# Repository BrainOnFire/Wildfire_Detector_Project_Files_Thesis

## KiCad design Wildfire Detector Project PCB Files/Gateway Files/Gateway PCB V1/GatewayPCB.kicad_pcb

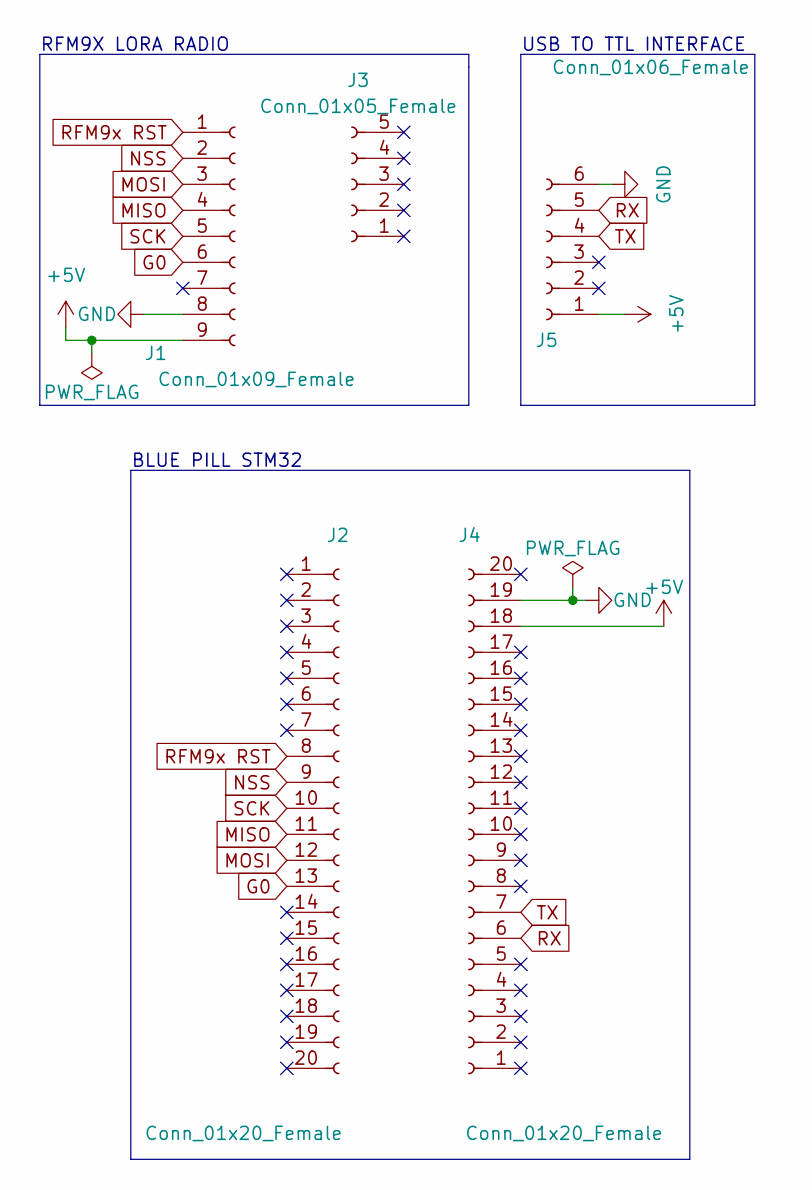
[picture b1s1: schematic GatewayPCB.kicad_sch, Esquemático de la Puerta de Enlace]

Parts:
J1: Conn_01x09_Female; PinSocket_1x09_P2.54mm_Vertical
J2, J4: Conn_01x20_Female; PinSocket_1x20_P2.54mm_Vertical
J3: Conn_01x05_Female; PinSocket_1x05_P2.54mm_Vertical
J5: Conn_01x06_Female; PinSocket_1x06_P2.54mm_Horizontal

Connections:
+5V: J1.9, J4.18, J5.1
G0: J1.6, J2.13
GND: J1.8, J4.19, J5.6
MISO: J1.4, J2.11
MOSI: J1.3, J2.12
NSS: J1.2, J2.9
RFM9x RST: J1.1, J2.8
RX: J4.6, J5.5
SCK: J1.5, J2.10
TX: J4.7, J5.4

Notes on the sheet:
RFM9X LORA RADIO
USB TO TTL INTERFACE
BLUE PILL STM32

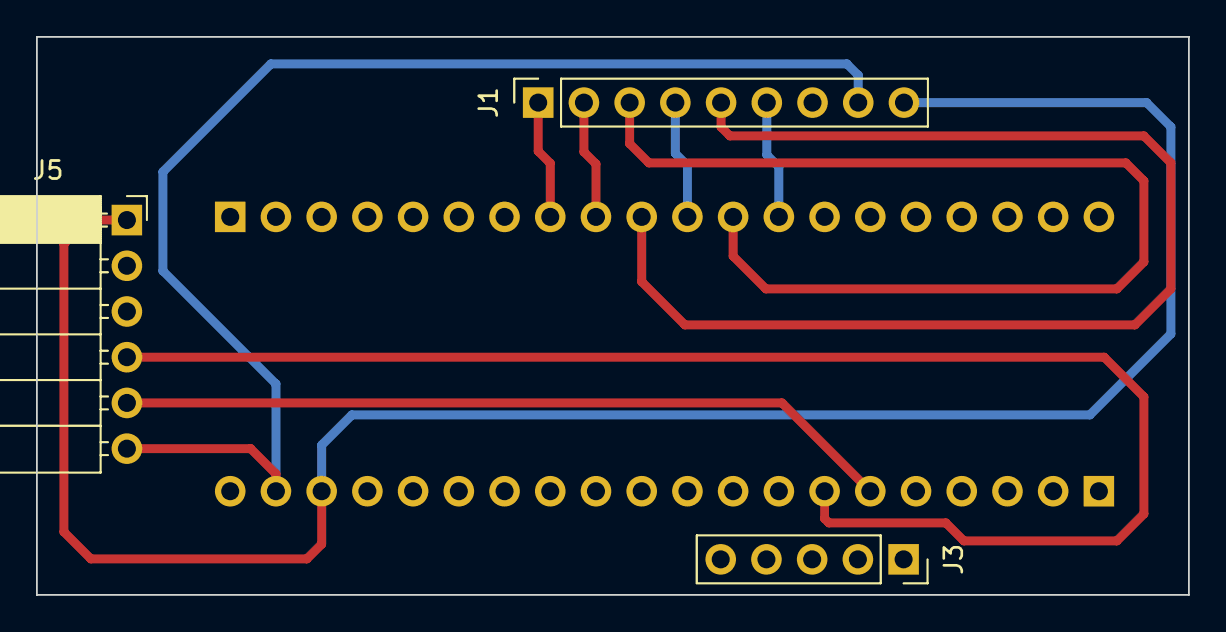
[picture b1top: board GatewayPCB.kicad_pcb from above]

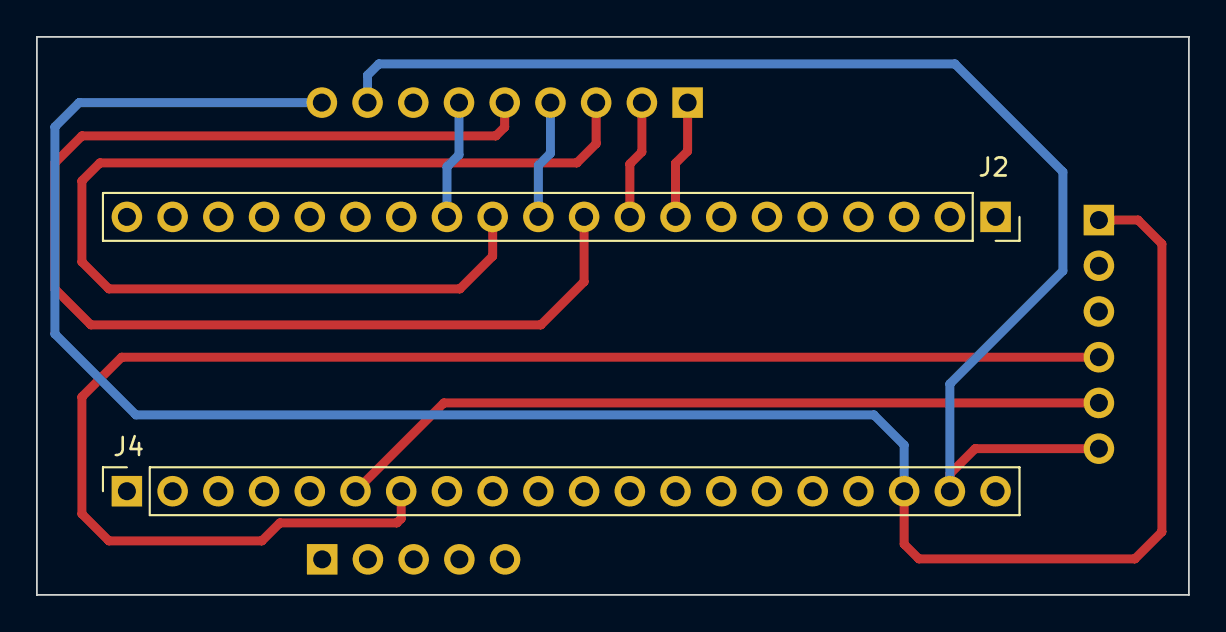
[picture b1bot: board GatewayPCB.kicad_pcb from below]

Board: 2 copper layers, 64.0 x 31.0 mm, 5 parts (2 on the bottom side), 10 nets.

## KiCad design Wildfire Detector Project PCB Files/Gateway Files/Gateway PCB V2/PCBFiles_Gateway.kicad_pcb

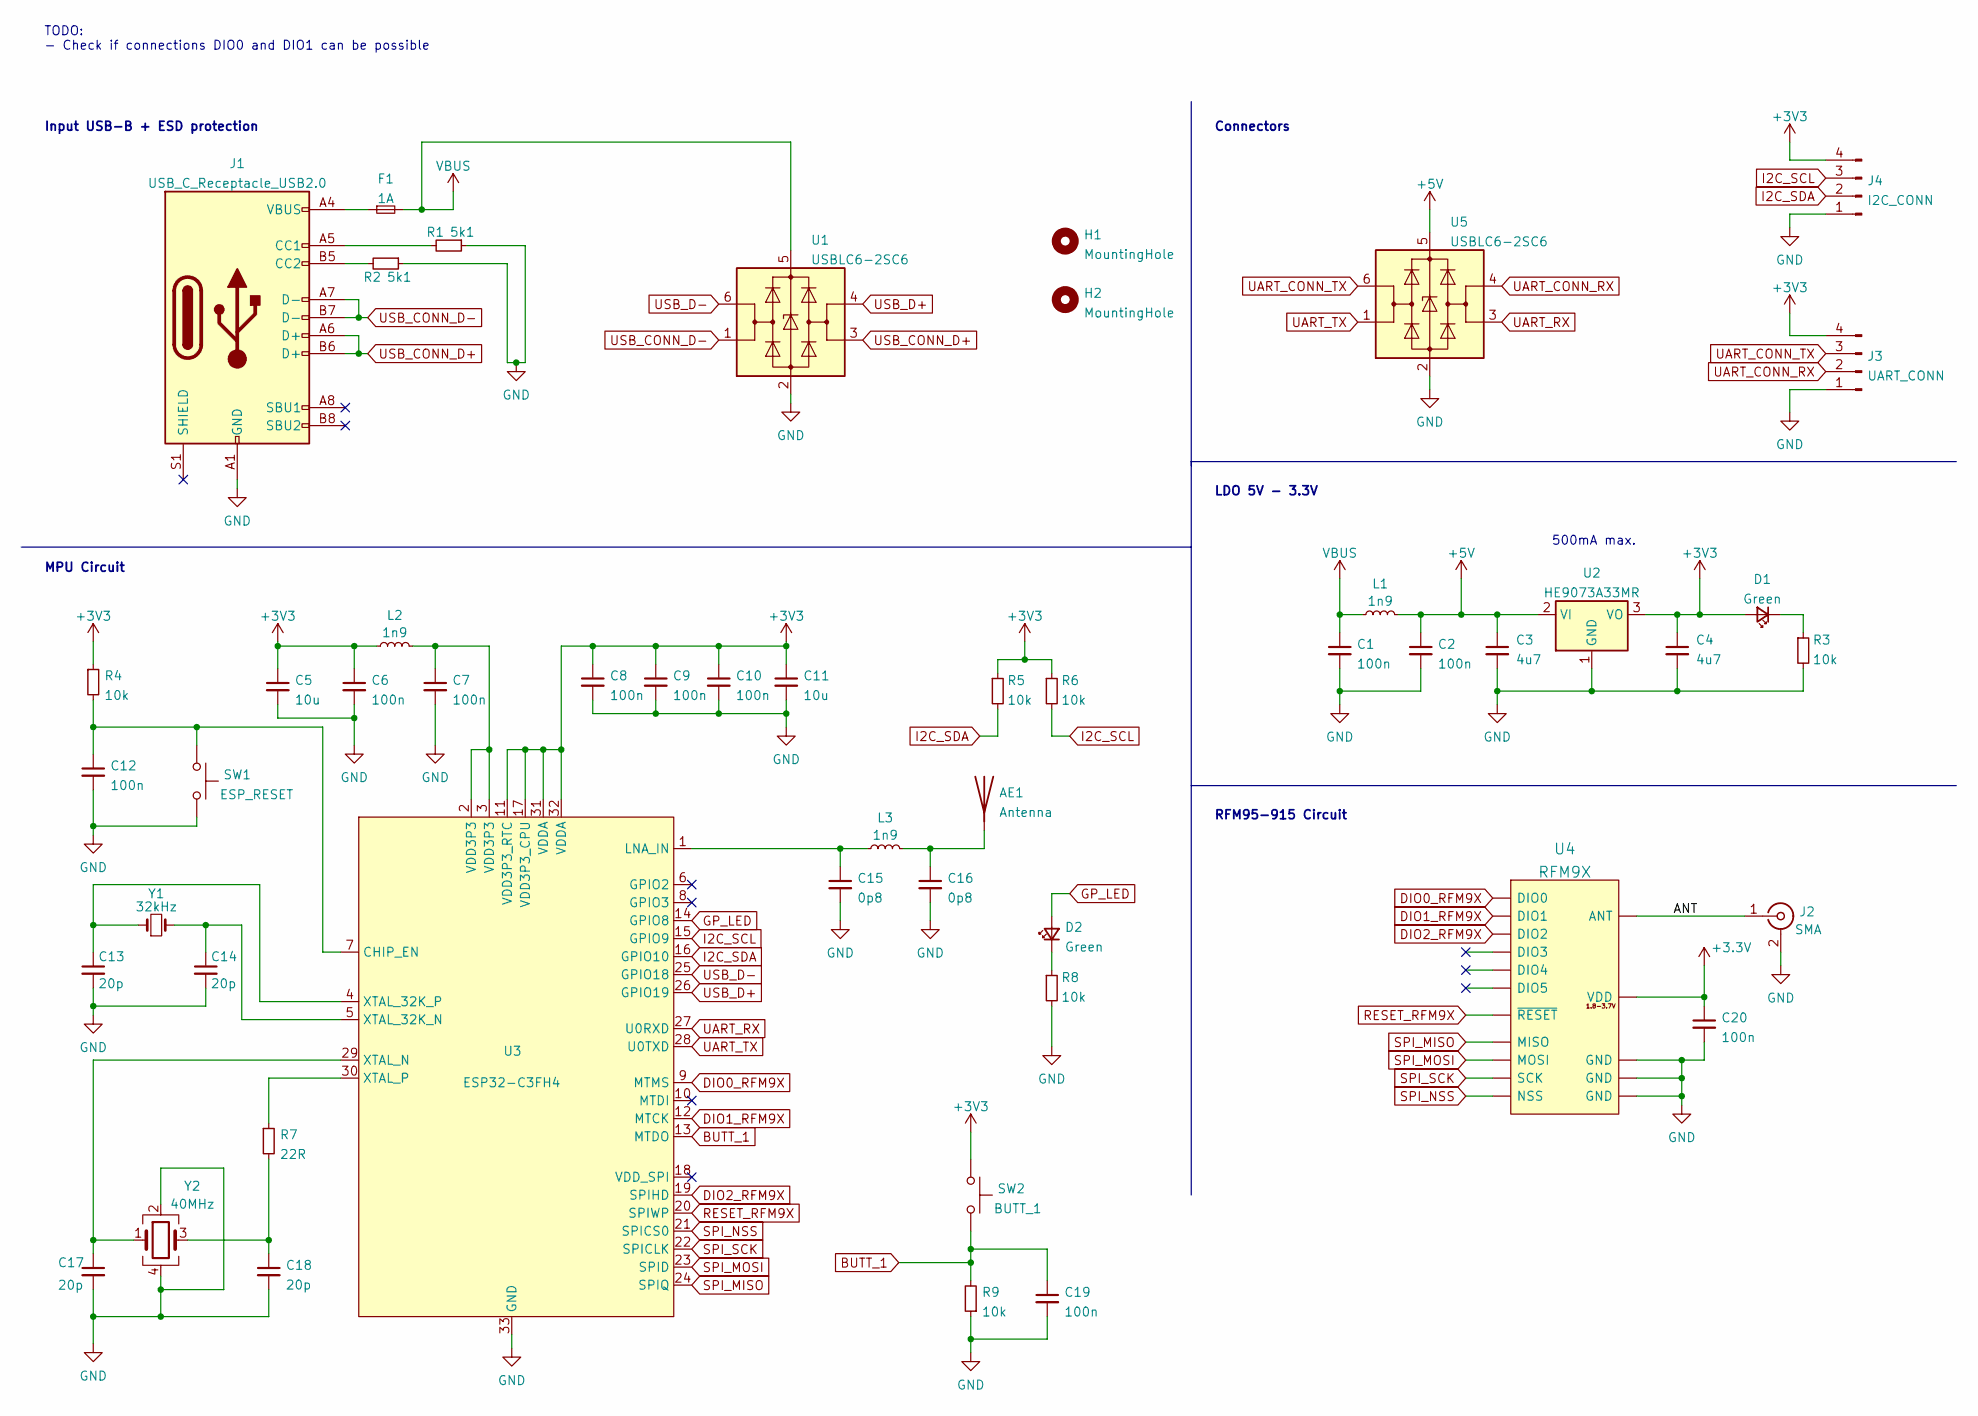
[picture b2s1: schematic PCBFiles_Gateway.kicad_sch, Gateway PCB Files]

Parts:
AE1: Antenna; PCB Meander Antenna
C1, C2: 100n; C_1206_3216Metric
C3, C4: 4u7; C_1206_3216Metric
C5, C11: 10u; C_0402_1005Metric
C6, C7, C8, C9, C10, C12, C19, C20: 100n; C_0402_1005Metric
C13, C14, C17, C18: 20p; C_0402_1005Metric
C15, C16: 0p8; C_0402_1005Metric
D1, D2: Green; C_0603_1608Metric
F1: 1A; Fuse_0603_1608Metric
H1, H2: MountingHole; MountingHole_2.2mm_M2_Pad
J1: USB_C_Receptacle_USB2.0; USB_C_Receptacle_HRO_TYPE-C-31-M-12
J2: SMA; SMA_Samtec_SMA-J-P-X-ST-EM1_EdgeMount
J3: UART_CONN; Molex_KK-254_AE-6410-04A_1x04_P2.54mm_Vertical
J4: I2C_CONN; PinHeader_1x04_P2.54mm_Vertical
L1, L2, L3: 1n9; L_0402_1005Metric
R1, R2: 5k1; R_0402_1005Metric
R3, R4, R5, R6, R8, R9: 10k; R_0805_2012Metric
R7: 22R; R_0402_1005Metric
SW1: ESP_RESET; SW_SPST_B3U-1000P
SW2: BUTT_1; SW_SPST_B3U-1000P
U1, U5: USBLC6-2SC6; SOT-23-6
U2: HE9073A33MR; SOT-23
U3: ESP32-C3FH4; QFN-32-1EP_5x5mm_P0.5mm_EP3.7x3.7mm
U4: RFM9X; RFM9X-SMD; LCSC Part # C2844473
Y1: 32kHz; Crystal_SMD_3215-2Pin_3.2x1.5mm
Y2: 40MHz; Crystal_SMD_3225-4Pin_3.2x2.5mm

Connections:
+5V: C2.1, C3.1, L1.2, U2.2 (VI), U5.5 (VBUS)
/ANT: J2.1 (In), U4.9 (ANT)
BUTT_1: C19.1, R9.2, SW2.2, U3.13 (MTDO)
DIO0_RFM9X: U3.9 (MTMS), U4.14 (DIO0)
DIO1_RFM9X: U3.12 (MTCK), U4.15 (DIO1)
DIO2_RFM9X: U3.19 (SPIHD), U4.16 (DIO2)
GND: C1.2, C2.2, C3.2, C4.2, C5.2, C6.2, C7.2, C8.2, C9.2, C10.2, C11.2, C12.2, C13.2, C14.2, C15.2, C16.2, C17.2, C18.2, C19.2, C20.2, J1.A1 (GND), J1.A12 (GND), J1.B1 (GND), J1.B12 (GND), J2.2 (Ext), J3.1, J4.1, R1.1, R2.1, R3.2, R8.2, R9.1, SW1.2, U1.2 (GND), U2.1 (GND), U3.33 (GND), U4.1 (GND), U4.8 (GND), U4.10 (GND), U5.2 (GND), Y2.2, Y2.4
GP_LED: D2.2 (A), U3.14 (GPIO8)
I2C_SCL: J4.3, R6.2, U3.15 (GPIO9)
I2C_SDA: J4.2, R5.2, U3.16 (GPIO10)
unnamed: C7.1, L2.2, U3.2 (VDD3P3), U3.3 (VDD3P3)
unnamed: C12.1, R4.2, SW1.1, U3.7 (CHIP_EN)
unnamed: C13.1, U3.4 (XTAL_32K_P), Y1.1
unnamed: C14.1, U3.5 (XTAL_32K_N), Y1.2
unnamed: C15.1, L3.1, U3.1 (LNA_IN)
unnamed: AE1.1 (A), C16.1, L3.2
unnamed: C17.1, U3.29 (XTAL_N), Y2.1
unnamed: C18.1, R7.2, Y2.3
unnamed: D1.1 (K), R3.1
unnamed: D2.1 (K), R8.1
unnamed: F1.1, J1.A4 (VBUS), J1.A9 (VBUS), J1.B4 (VBUS), J1.B9 (VBUS)
unnamed: J1.A5 (CC1), R1.2
unnamed: J1.B5 (CC2), R2.2
unnamed: R7.1, U3.30 (XTAL_P)
RESET_RFM9X: U3.20 (SPIWP), U4.6 (~RESET)
SPI_MISO: U3.24 (SPIQ), U4.2 (MISO)
SPI_MOSI: U3.23 (SPID), U4.3 (MOSI)
SPI_NSS: U3.21 (SPICS0), U4.5 (NSS)
SPI_SCK: U3.22 (SPICLK), U4.4 (SCK)
UART_CONN_RX: J3.2, U5.4 (I/O2)
UART_CONN_TX: J3.3, U5.6 (I/O1)
UART_RX: U3.27 (U0RXD), U5.3 (I/O2)
UART_TX: U3.28 (U0TXD), U5.1 (I/O1)
USB_CONN_D+: J1.A6 (D+), J1.B6 (D+), U1.3 (I/O2)
USB_CONN_D-: J1.A7 (D-), J1.B7 (D-), U1.1 (I/O1)
USB_D+: U1.4 (I/O2), U3.26 (GPIO19)
USB_D-: U1.6 (I/O1), U3.25 (GPIO18)
VBUS: C1.1, F1.2, L1.1, U1.5 (VBUS)

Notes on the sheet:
Connectors
RFM95-915 Circuit
500mA max.
MPU Circuit
TODO: - Check if connections DIO0 and DIO1 can be possible
LDO 5V - 3.3V
Input USB-B + ESD protection

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
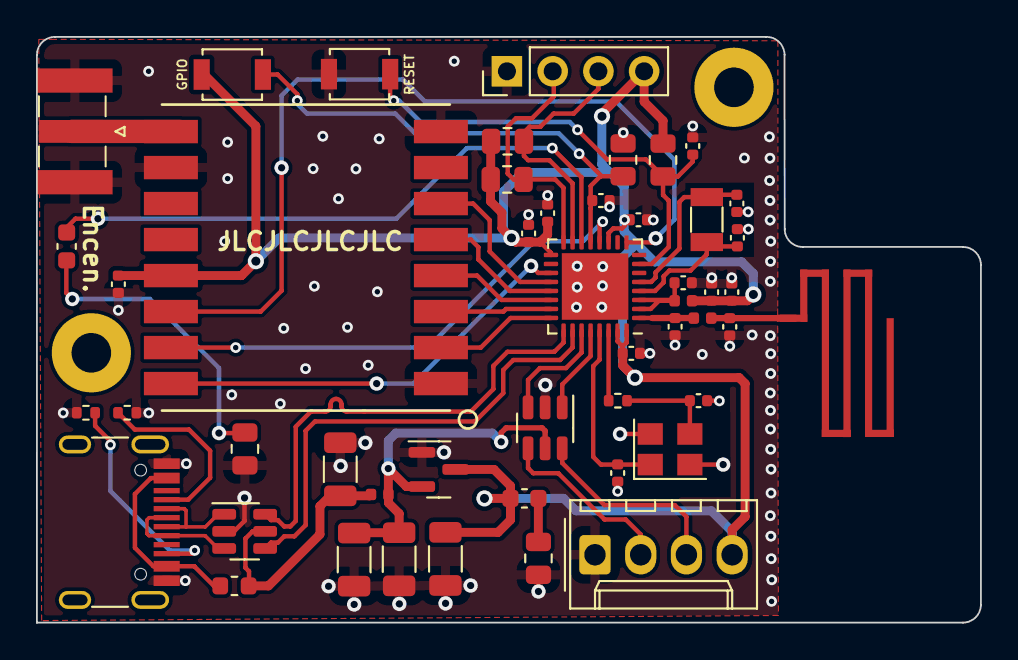
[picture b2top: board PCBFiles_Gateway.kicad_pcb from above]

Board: 4 copper layers, 52.4 x 32.5 mm, 51 parts (0 on the bottom side), 39 nets.

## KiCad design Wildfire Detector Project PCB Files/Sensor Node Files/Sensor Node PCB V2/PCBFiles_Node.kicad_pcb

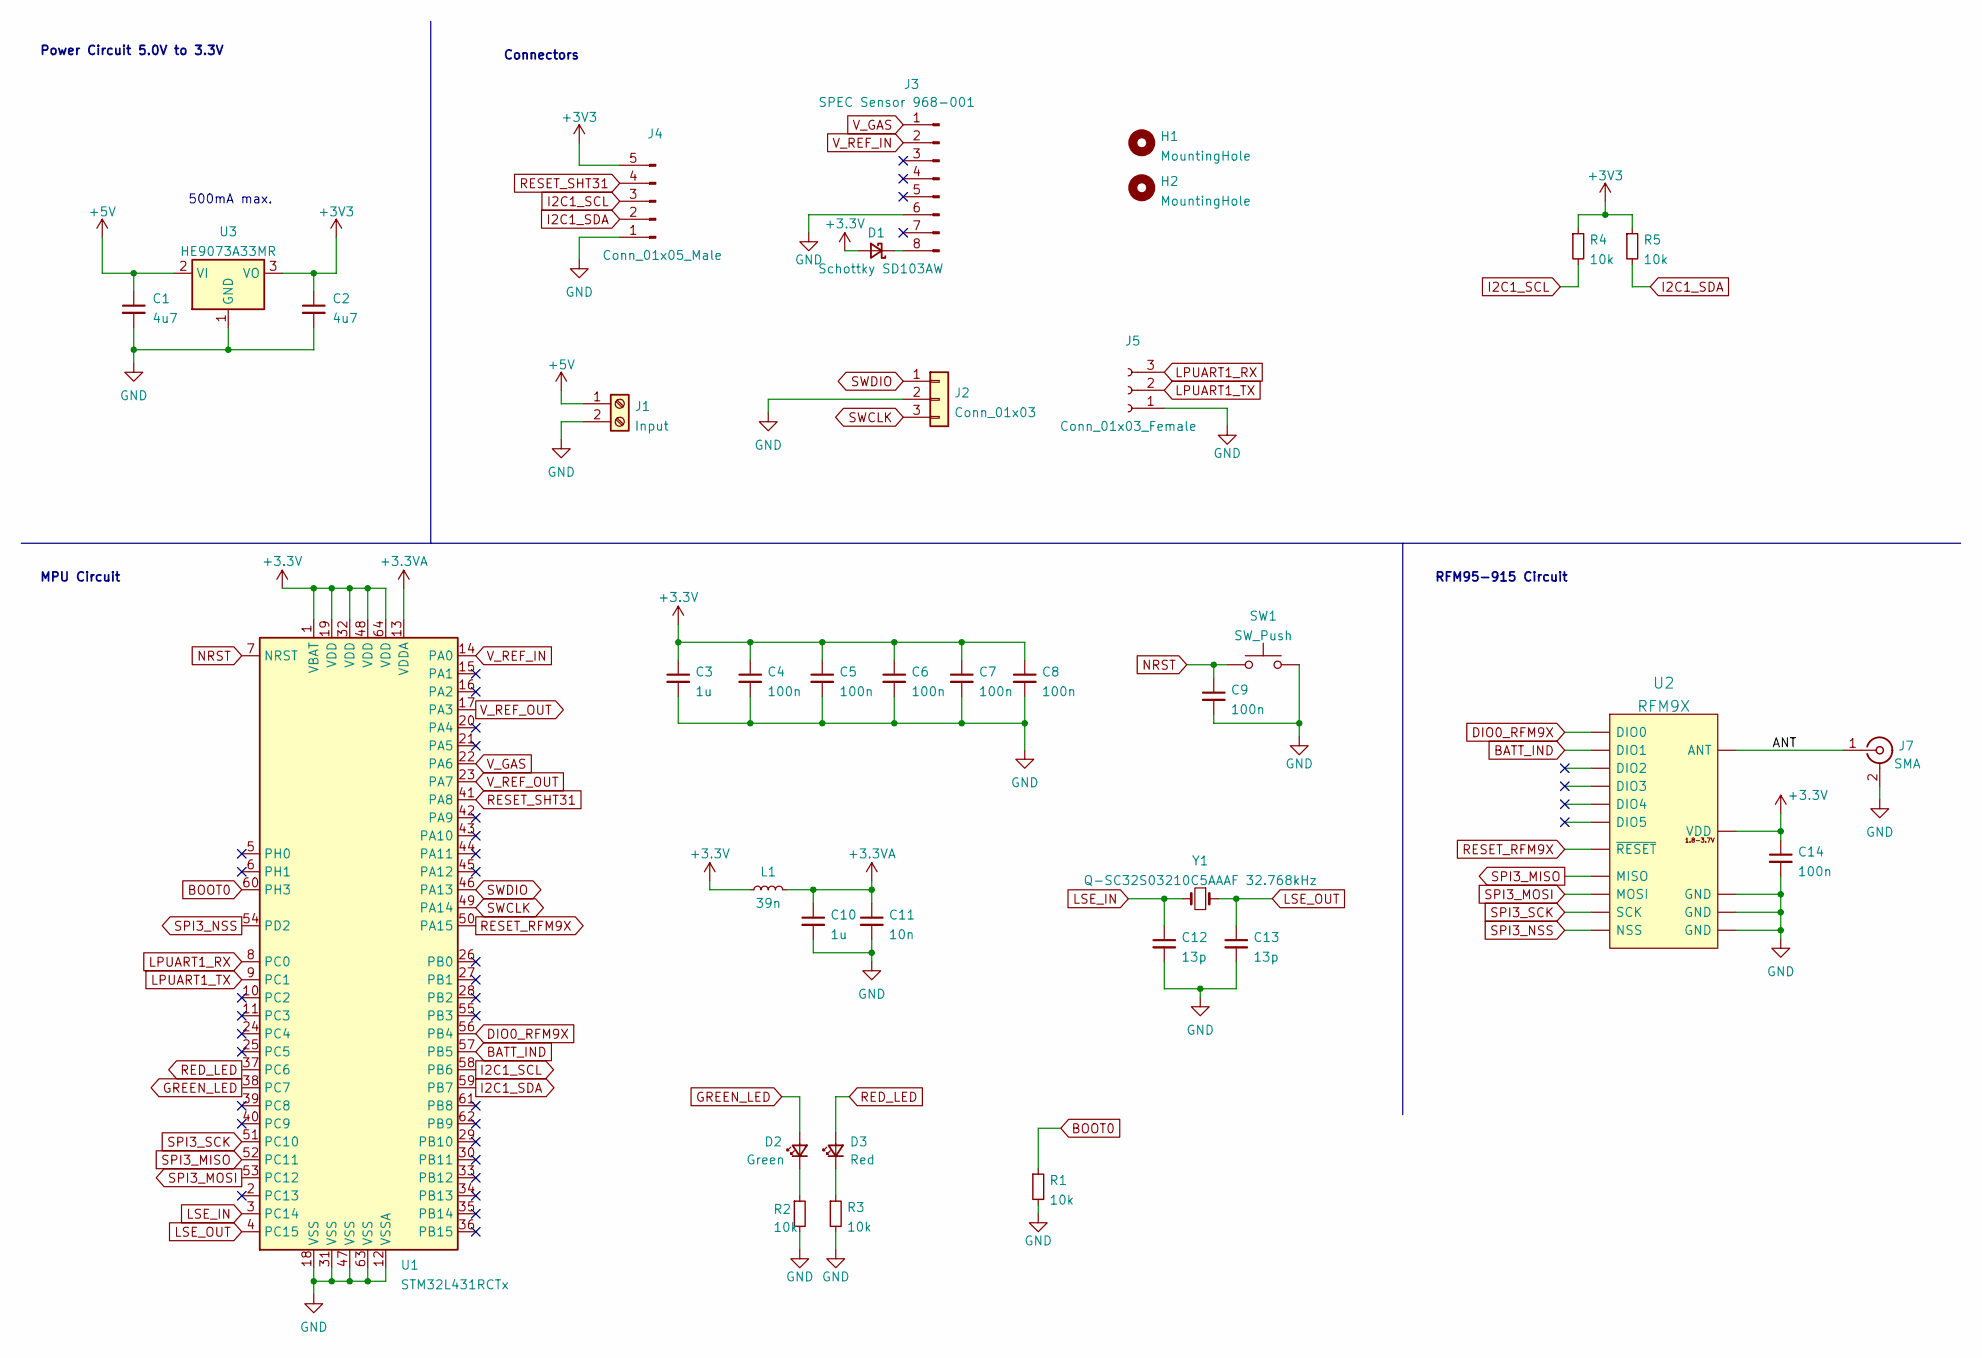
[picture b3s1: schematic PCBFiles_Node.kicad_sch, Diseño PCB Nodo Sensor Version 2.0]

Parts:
C1, C2: 4u7; C_1206_3216Metric
C3, C10: 1u; C_0402_1005Metric; LCSC Part # C52923
C4, C5, C6, C7, C8, C9, C14: 100n; C_0402_1005Metric; LCSC Part # C307331
C11: 10n; C_0402_1005Metric; LCSC Part # C15195
C12, C13: 13p; C_0402_1005Metric; LCSC Part # C48936
D1: Schottky SD103AW; D_SOD-123; LCSC Part # C191023
D2: Green; LED_0603_1608Metric; LCSC Part # C118334
D3: Red; LED_0603_1608Metric; LCSC Part # C118330
H1, H2: MountingHole; MountingHole_2.2mm_M2_Pad
J1: Input; TerminalBlock_bornier-2_P5.08mm
J2: Conn_01x03; PinSocket_1x03_P2.54mm_Vertical
J3: SPEC Sensor 968-001; PinHeader_1x08_P2.54mm_Horizontal
J4: Conn_01x05_Male; PinSocket_1x05_P2.54mm_Vertical
J5: Conn_01x03_Female; PinSocket_1x03_P2.54mm_Horizontal
J7: SMA; SMA_Samtec_SMA-J-P-X-ST-EM1_EdgeMount
L1: 39n; L_0402_1005Metric; LCSC Part # C335623
R1: 10k; R_0805_2012Metric; LCSC Part # C25744
R2, R3, R4, R5: 10k; R_0805_2012Metric; LCSC Part # C21190
SW1: SW_Push; SW_SPST_B3U-1000P; LCSC Part # B3U-1000P
U1: STM32L431RCTx; LQFP-64_10x10mm_P0.5mm; LCSC Part # C92468
U2: RFM9X; RFM9X-SMD; LCSC Part # C2844473
U3: HE9073A33MR; SOT-23
Y1: Q-SC32S03210C5AAAF 32.768kHz; Q13FC1350000400; LCSC Part # C32346

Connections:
+3.3VA: C10.1, C11.1, L1.2, U1.13 (VDDA)
+5V: C1.1, J1.1, U3.2 (VI)
/ANT: J7.1 (In), U2.16 (ANT)
BATT_IND: U1.57 (PB5), U2.10 (DIO1)
BOOT0: R1.1, U1.60 (PH3)
DIO0_RFM9X: U1.56 (PB4), U2.11 (DIO0)
GND: C1.2, C2.2, C3.2, C4.2, C5.2, C6.2, C7.2, C8.2, C9.2, C10.2, C11.2, C12.2, C13.2, C14.2, J1.2, J2.2, J3.6, J4.1, J5.1, J7.2 (Ext), R1.2, R2.2, R3.2, SW1.2, U1.12 (VSSA), U1.18 (VSS), U1.31 (VSS), U1.47 (VSS), U1.63 (VSS), U2.1 (GND), U2.8 (GND), U2.15 (GND), U3.1 (GND)
GREEN_LED: D2.2 (A), U1.38 (PC7)
I2C1_SCL: J4.3, R4.2, U1.58 (PB6)
I2C1_SDA: J4.2, R5.2, U1.59 (PB7)
LPUART1_RX: J5.3, U1.8 (PC0)
LPUART1_TX: J5.2, U1.9 (PC1)
LSE_IN: C12.1, U1.3 (PC14), Y1.2
LSE_OUT: C13.1, U1.4 (PC15), Y1.1
NRST: C9.1, SW1.1, U1.7 (NRST)
unnamed: D1.1 (K), J3.8
unnamed: D2.1 (K), R2.1
unnamed: D3.1 (K), R3.1
RED_LED: D3.2 (A), U1.37 (PC6)
RESET_RFM9X: U1.50 (PA15), U2.6 (~RESET)
RESET_SHT31: J4.4, U1.41 (PA8)
SPI3_MISO: U1.52 (PC11), U2.2 (MISO)
SPI3_MOSI: U1.53 (PC12), U2.3 (MOSI)
SPI3_NSS: U1.54 (PD2), U2.5 (NSS)
SPI3_SCK: U1.51 (PC10), U2.4 (SCK)
SWCLK: J2.3, U1.49 (PA14)
SWDIO: J2.1, U1.46 (PA13)
V_GAS: J3.1, U1.22 (PA6)
V_REF_IN: J3.2, U1.14 (PA0)
V_REF_OUT: U1.17 (PA3), U1.23 (PA7)

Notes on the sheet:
RFM95-915 Circuit
500mA max.
MPU Circuit
Connectors
Power Circuit 5.0V to 3.3V

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
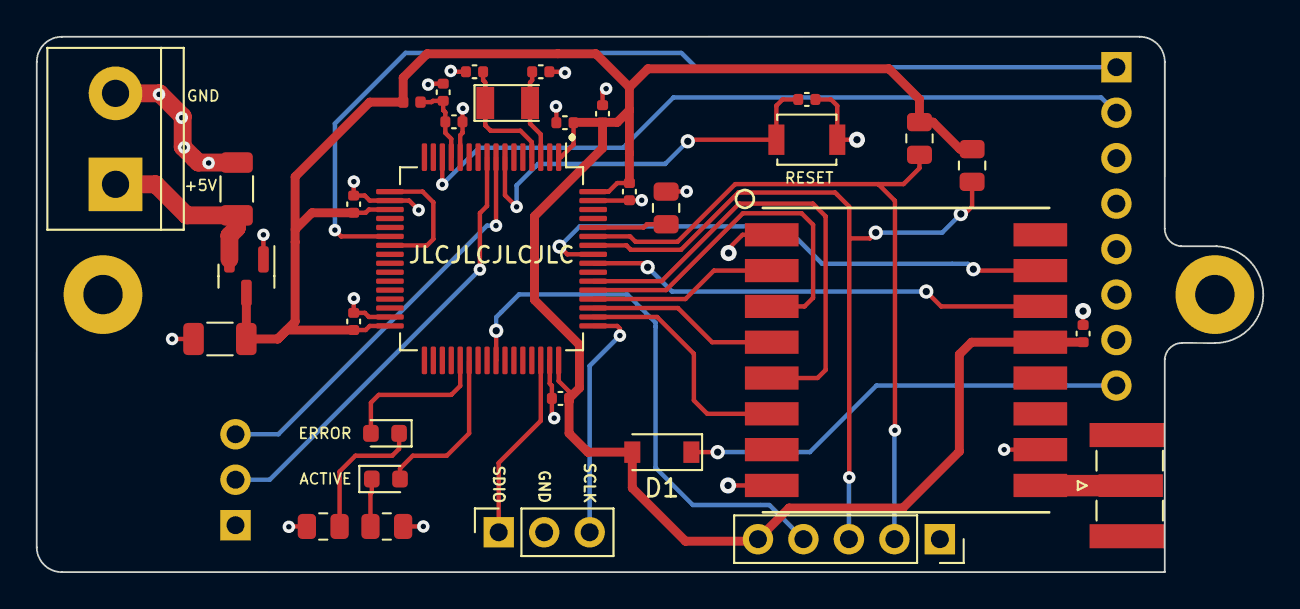
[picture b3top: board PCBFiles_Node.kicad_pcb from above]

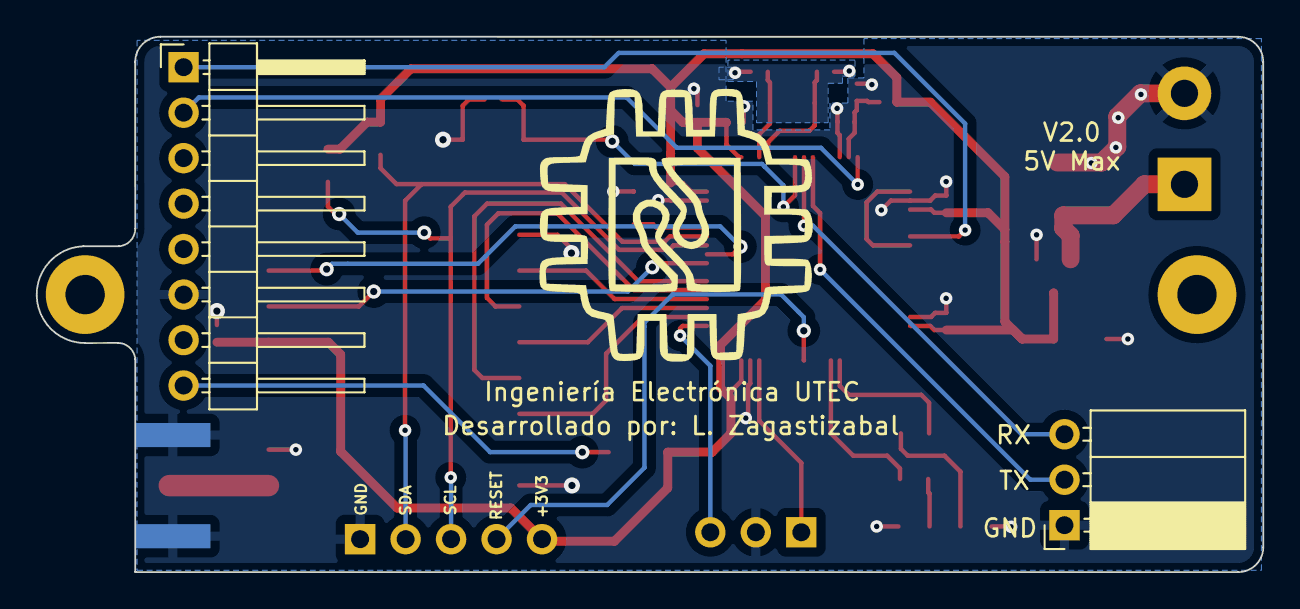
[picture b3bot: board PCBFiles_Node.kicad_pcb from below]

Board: 2 copper layers, 68.5 x 29.9 mm, 36 parts (2 on the bottom side), 31 nets.

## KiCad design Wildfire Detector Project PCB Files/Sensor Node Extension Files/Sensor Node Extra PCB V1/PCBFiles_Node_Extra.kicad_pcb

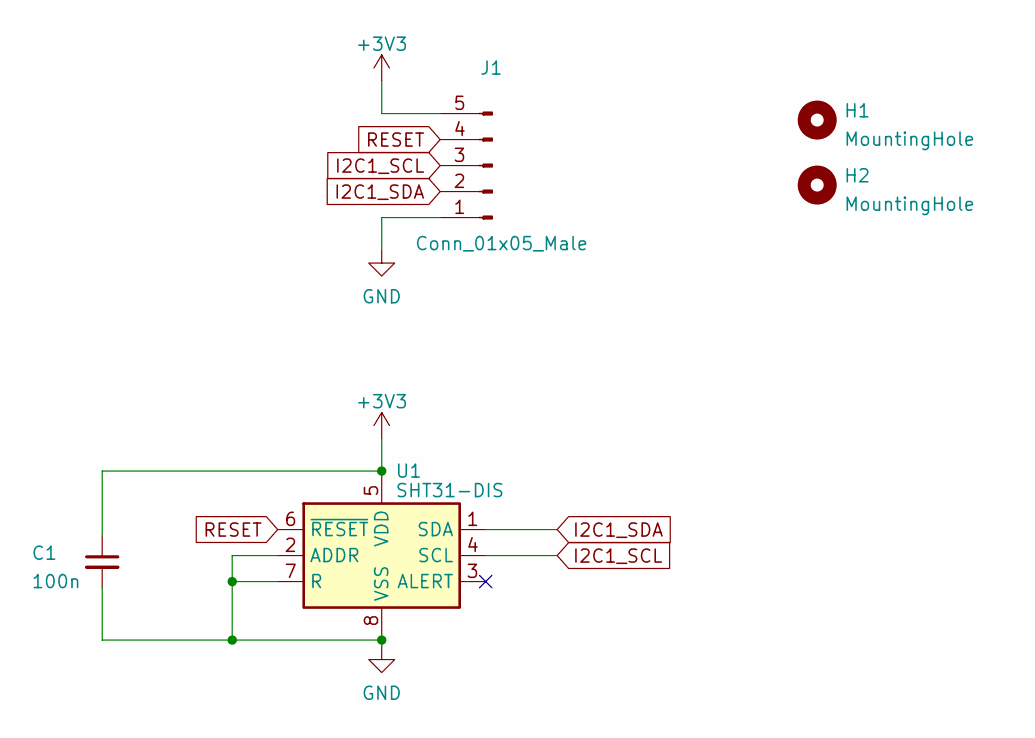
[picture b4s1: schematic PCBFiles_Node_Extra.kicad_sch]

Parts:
C1: 100n; C_0402_1005Metric; LCSC Part # C307331
H1, H2: MountingHole; MountingHole_2.2mm_M2_Pad
J1: Conn_01x05_Male; PinSocket_1x05_P2.54mm_Vertical
U1: SHT31-DIS; Sensirion_DFN-8-1EP_2.5x2.5mm_P0.5mm_EP1.1x1.7mm

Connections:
+3V3: C1.1, J1.5, U1.5 (VDD)
GND: C1.2, J1.1, U1.2 (ADDR), U1.7 (R), U1.8 (VSS), U1.9 (VSS)
I2C1_SCL: J1.3, U1.4 (SCL)
I2C1_SDA: J1.2, U1.1 (SDA)
RESET: J1.4, U1.6 (~RESET)

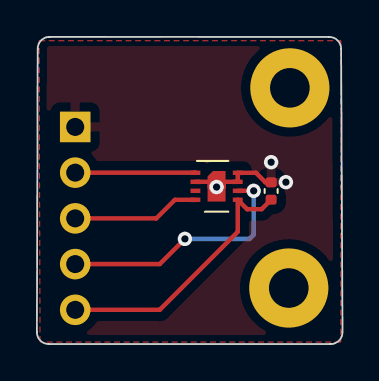
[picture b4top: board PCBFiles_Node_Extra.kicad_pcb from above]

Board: 2 copper layers, 17.0 x 17.1 mm, 5 parts (1 on the bottom side), 5 nets.

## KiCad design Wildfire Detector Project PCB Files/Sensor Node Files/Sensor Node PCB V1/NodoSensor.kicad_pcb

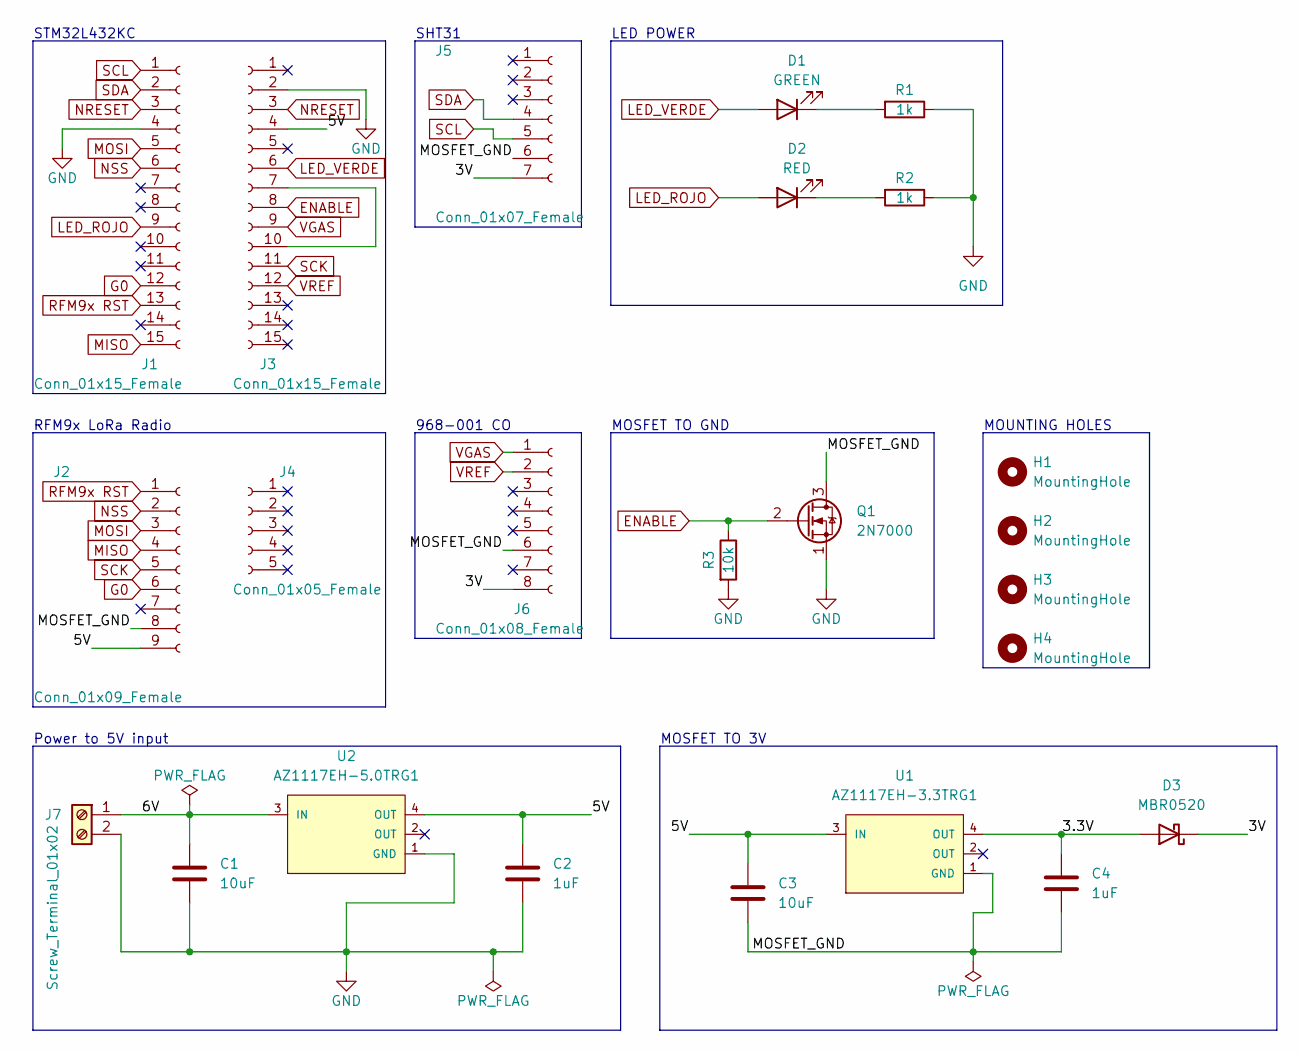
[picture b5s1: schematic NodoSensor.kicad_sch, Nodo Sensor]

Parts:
C1, C3: 10uF; CP_Radial_D5.0mm_P2.50mm
C2, C4: 1uF; CP_Radial_D5.0mm_P2.50mm
D1: GREEN; LED_D5.0mm
D2: RED; LED_D5.0mm
D3: MBR0520; D_SOD-123
H1, H2, H3, H4: MountingHole; MountingHole_3.2mm_M3
J1, J3: Conn_01x15_Female; PinSocket_1x15_P2.54mm_Vertical
J2: Conn_01x09_Female; PinSocket_1x09_P2.54mm_Vertical
J4: Conn_01x05_Female; PinSocket_1x05_P2.54mm_Vertical
J5: Conn_01x07_Female; PinSocket_1x07_P2.54mm_Vertical
J6: Conn_01x08_Female; PinSocket_1x08_P2.54mm_Vertical
J7: Screw_Terminal_01x02; TerminalBlock_bornier-2_P5.08mm
Q1: 2N7000; TO-92_Inline
R1, R2: 1k; R_Axial_DIN0207_L6.3mm_D2.5mm_P10.16mm_Horizontal
R3: 10k; R_Axial_DIN0207_L6.3mm_D2.5mm_P10.16mm_Horizontal
U1: AZ1117EH-3.3TRG1; SOT230P700X180-4N; PARTREV 3-2
U2: AZ1117EH-5.0TRG1; SOT230P700X180-4N

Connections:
/3.3V: C4.1, D3.2 (A), U1.4 (OUT)
/3V: D3.1 (K), J5.7, J6.8
/5V: C2.1, C3.1, J2.9, J3.4, U1.3 (IN), U2.4 (OUT)
/6V: C1.1, J7.1, U2.3 (IN)
/MOSFET_GND: C3.2, C4.2, J2.8, J5.6, J6.6, Q1.3 (D), U1.1 (GND)
ENABLE: J3.8, Q1.2 (G), R3.1
G0: J1.12, J2.6
GND: C1.2, C2.2, J1.4, J3.2, J7.2, Q1.1 (S), R1.1, R2.1, R3.2, U2.1 (GND)
LED_ROJO: D2.2 (A), J1.9
LED_VERDE: D1.2 (A), J3.6
MISO: J1.15, J2.4
MOSI: J1.5, J2.3
NRESET: J1.3, J3.3
NSS: J1.6, J2.2
unnamed: D1.1 (K), R1.2
unnamed: D2.1 (K), R2.2
unnamed: J3.7, J3.10
RFM9x RST: J1.13, J2.1
SCK: J2.5, J3.11
SCL: J1.1, J5.5
SDA: J1.2, J5.4
VGAS: J3.9, J6.1
VREF: J3.12, J6.2

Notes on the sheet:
SHT31
STM32L432KC
Power to 5V input
MOSFET TO 3V
968-001 CO
MOUNTING HOLES
RFM9x LoRa Radio
LED POWER
MOSFET TO GND

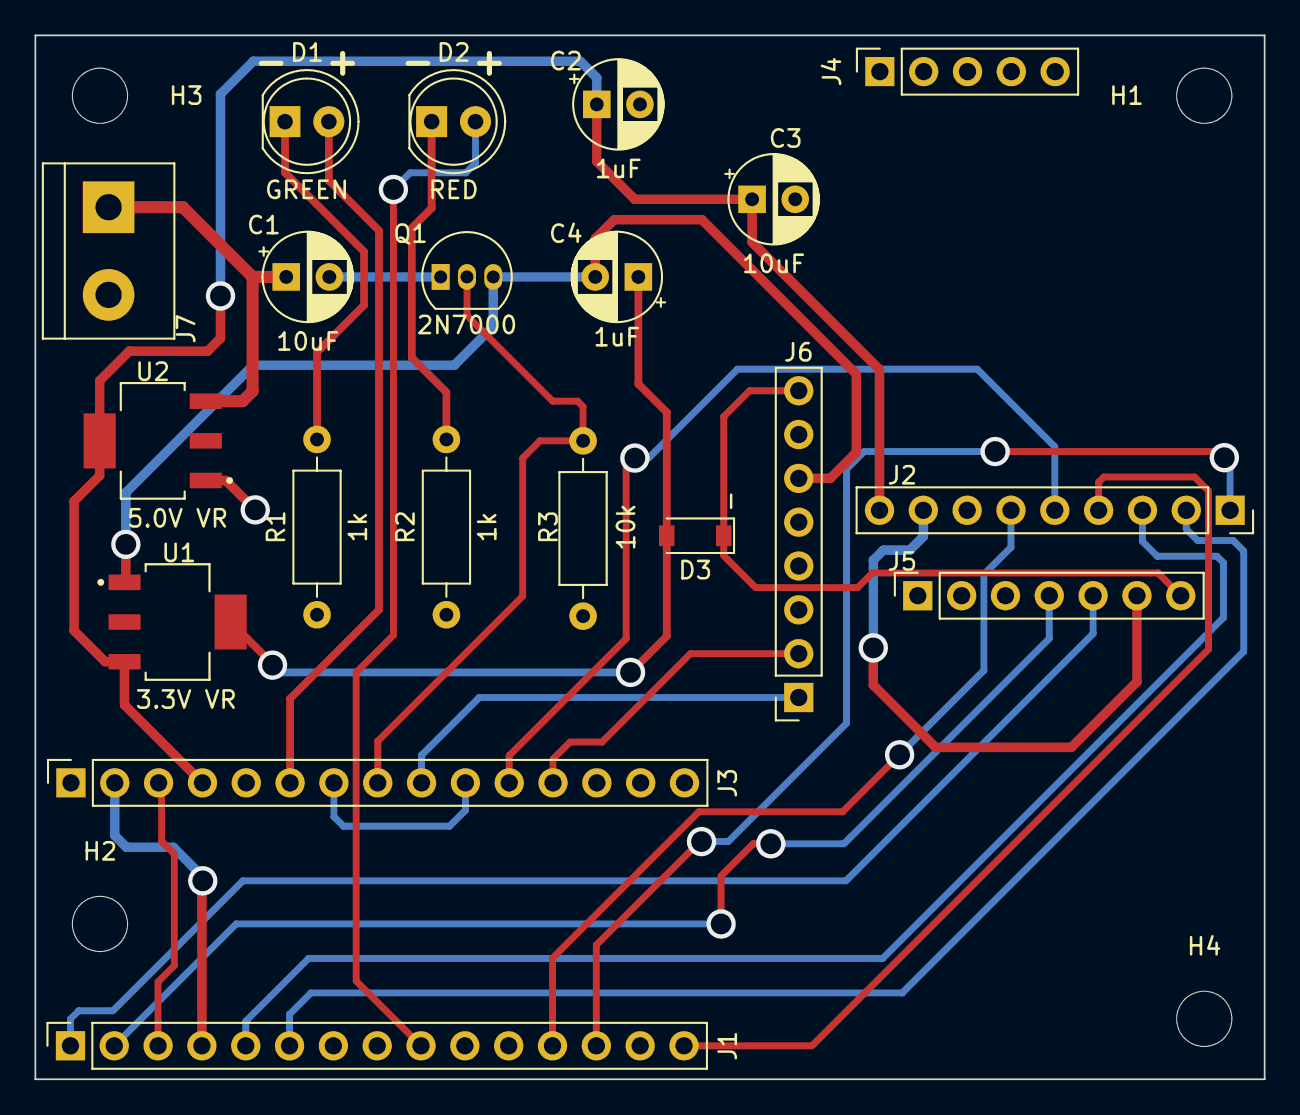
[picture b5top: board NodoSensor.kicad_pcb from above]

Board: 2 copper layers, 71.2 x 60.5 mm, 24 parts (0 on the bottom side), 23 nets.

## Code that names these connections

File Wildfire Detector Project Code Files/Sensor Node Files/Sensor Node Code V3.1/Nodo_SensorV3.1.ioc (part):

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Mcu.Name=STM32L431R(B-C)Tx
Mcu.Package=LQFP64
Mcu.UserName=STM32L431RCTx
PA0.GPIOParameters=GPIO_Label
PA0.GPIO_Label=V_REF_IN
PA0.Mode=Follower
PA0.Signal=OPAMP1_VINP
PA13\ (JTMS-SWDIO).GPIOParameters=GPIO_Label
PA13\ (JTMS-SWDIO).GPIO_Label=SWDIO
PA13\ (JTMS-SWDIO).Mode=Serial_Wire
PA13\ (JTMS-SWDIO).Signal=SYS_JTMS-SWDIO
PA14\ (JTCK-SWCLK).GPIOParameters=GPIO_Label
PA14\ (JTCK-SWCLK).GPIO_Label=SWCLK
PA14\ (JTCK-SWCLK).Mode=Serial_Wire
PA14\ (JTCK-SWCLK).Signal=SYS_JTCK-SWCLK
PA15\ (JTDI).GPIOParameters=PinState,GPIO_Label
PA15\ (JTDI).GPIO_Label=RESET_RFM9X
PA15\ (JTDI).PinState=GPIO_PIN_SET
PA15\ (JTDI).Signal=GPIO_Output
PA3.GPIOParameters=GPIO_Label
PA3.GPIO_Label=V_REF_OUT
PA3.Mode=Follower
PA3.Signal=OPAMP1_VOUT
PA6.GPIOParameters=GPIO_Label
PA6.GPIO_Label=V_GAS
PA6.Signal=ADCx_IN11
PA7.GPIOParameters=GPIO_Label
PA7.GPIO_Label=V_REF_OUT_IN
PA7.Signal=ADCx_IN12
PA8.GPIOParameters=GPIO_Label
PA8.GPIO_Label=RESET_SHT31
PA8.Signal=GPIO_Output
PB4\ (NJTRST).GPIOParameters=GPIO_Label
PB4\ (NJTRST).GPIO_Label=DIO0_RFM9X
PB4\ (NJTRST).Signal=GPIO_Output
PB5.GPIOParameters=GPIO_Label
PB5.GPIO_Label=BATT_IND
PB5.Signal=GPXTI5
PB6.Mode=I2C
PB6.Signal=I2C1_SCL
PB7.Mode=I2C
PB7.Signal=I2C1_SDA
PC0.Mode=Asynchronous
PC0.Signal=LPUART1_RX
PC1.Mode=Asynchronous
PC1.Signal=LPUART1_TX
PC10.Mode=Full_Duplex_Master
PC10.Signal=SPI3_SCK
PC11.Mode=Full_Duplex_Master
PC11.Signal=SPI3_MISO
PC12.Mode=Full_Duplex_Master
PC12.Signal=SPI3_MOSI
PC14-OSC32_IN\ (PC14).Mode=LSE-External-Oscillator
PC14-OSC32_IN\ (PC14).Signal=RCC_OSC32_IN
PC15-OSC32_OUT\ (PC15).Mode=LSE-External-Oscillator
PC15-OSC32_OUT\ (PC15).Signal=RCC_OSC32_OUT
PC6.GPIOParameters=GPIO_Label
PC6.GPIO_Label=LED_ROJO
PC6.Signal=GPIO_Output
PC7.GPIOParameters=GPIO_Label
PC7.GPIO_Label=LED_VERDE
PC7.Signal=GPIO_Output
PD2.GPIOParameters=PinState,GPIO_Label
PD2.GPIO_Label=SPI3_NSS
PD2.PinState=GPIO_PIN_SET
PD2.Signal=GPIO_Output
RCC.HSE_VALUE=8000000
RCC.SYSCLKFreq_VALUE=2000000
board=custom

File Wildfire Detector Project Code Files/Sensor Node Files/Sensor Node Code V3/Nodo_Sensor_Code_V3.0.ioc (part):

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Mcu.Name=STM32L432K(B-C)Ux
Mcu.Package=UFQFPN32
Mcu.UserName=STM32L432KCUx
PA0.GPIOParameters=GPIO_Label
PA0.GPIO_Label=V_REF_IN
PA0.Mode=Follower
PA0.Signal=OPAMP1_VINP
PA10.Mode=I2C
PA10.Signal=I2C1_SDA
PA11.Mode=Device
PA11.Signal=USB_DM
PA12.Mode=Device
PA12.Signal=USB_DP
PA13\ (JTMS-SWDIO).GPIOParameters=GPIO_Label
PA13\ (JTMS-SWDIO).GPIO_Label=SWDIO
PA13\ (JTMS-SWDIO).Mode=Serial_Wire
PA13\ (JTMS-SWDIO).Signal=SYS_JTMS-SWDIO
PA14\ (JTCK-SWCLK).GPIOParameters=GPIO_Label
PA14\ (JTCK-SWCLK).GPIO_Label=SWCLCK
PA14\ (JTCK-SWCLK).Mode=Serial_Wire
PA14\ (JTCK-SWCLK).Signal=SYS_JTCK-SWCLK
PA2.GPIOParameters=GPIO_Label
PA2.GPIO_Label=GREEN_LED
PA2.Signal=GPIO_Output
PA3.GPIOParameters=GPIO_Label
PA3.GPIO_Label=V_REF_OUT
PA3.Mode=Follower
PA3.Signal=OPAMP1_VOUT
PA4.GPIOParameters=GPIO_Label
PA4.GPIO_Label=V_REF_OUT_IN
PA4.Signal=ADCx_IN9
PA5.GPIOParameters=GPIO_Label
PA5.GPIO_Label=V_GAS
PA5.Signal=ADCx_IN10
PA6.GPIOParameters=GPIO_Label
PA6.GPIO_Label=RESET_RFM9X
PA6.Signal=GPIO_Output
PA7.GPIOParameters=GPIO_Label
PA7.GPIO_Label=RED_LED
PA7.Signal=GPIO_Output
PA8.GPIOParameters=GPIO_Label
PA8.GPIO_Label=SPI3_NSS
PA8.Signal=GPIO_Output
PA9.Mode=I2C
PA9.Signal=I2C1_SCL
PB3\ (JTDO-TRACESWO).Mode=Full_Duplex_Master
PB3\ (JTDO-TRACESWO).Signal=SPI3_SCK
PB4\ (NJTRST).Mode=Full_Duplex_Master
PB4\ (NJTRST).Signal=SPI3_MISO
PB5.Mode=Full_Duplex_Master
PB5.Signal=SPI3_MOSI
PC14-OSC32_IN\ (PC14).Mode=LSE-External-Oscillator
PC14-OSC32_IN\ (PC14).Signal=RCC_OSC32_IN
PC15-OSC32_OUT\ (PC15).Mode=LSE-External-Oscillator
PC15-OSC32_OUT\ (PC15).Signal=RCC_OSC32_OUT
RCC.HSE_VALUE=8000000
RCC.SYSCLKFreq_VALUE=80000000
RCC.SYSCLKSource=RCC_SYSCLKSOURCE_PLLCLK
board=custom

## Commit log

2023-12-11 Added Sensor Node Code V2
